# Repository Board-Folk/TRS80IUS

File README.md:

# TRS80IUS

A remake of the TRS-80 Model I 1700069G motherboard.

This reposistory contains the BOM, gerbers and Kicad files for a remake of the final 'G' version (as far as we know), of the TRS-80 Model I original American version motherboard and some related projects and files. This project spawned after publishing its sister project, a recreation of the [TEC, Japanese version which can be found here](https://github.com/Board-Folk/TRS80IJP).

This is intended as a replica, but additional headers have been provided for the common modification of the 8 bit character set - "BIT6" and "D6" - and "L8" for connection of a character ROM substitute like the Gendon3 module. If original operation with 7-bit characters is required, solder jumper UC should be connected. No additional factory bodge capacitors were added either, for example the ones for the horizontal and vertical sync stabalization. You'll still need to add those yourself.

## Version 1.1 Bill-of-Materials

All resistors 1/4W unless specified. Suggested substitutes might be wrong. Any feedback welcome.

|Qty|Reference(s)|Value|Type|Notes|
|:--:|:--:|:--:|:--:|:--:|
|1|C1|220uF 16V|Electrolytic Capacitor||
|6|C2, C4, C5, C10, C11, C57|10uF 16V|Electrolytic Capacitor||
|1|C6|100uF 16V|Electrolytic Capacitor||
|1|C8|2200uF 35V|Electrolytic Capacitor (Axial)||
|1|C9|10000uF 16V|Electrolytic Capacitor (Axial)||
|1|C42|22uF 16V|Electrolytic Capacitor||
|1|C26|0.047uF|Film Capacitor||
|1|C27|0.022uF|Film Capacitor||
|35|C16-C19, C22, C23, C28-C34, C35-C39, C40, C41, C44-C56, C58, C59|100nF|Ceramic Capacitor||
|4|C3, C7, C14, C15|10nF|Ceramic Capacitor||
|2|C12, C13|470pF|Ceramic Capacitor||
|1|C20|330pF|Ceramic Capacitor||
|1|C21|750pF|Ceramic Capacitor||
|2|C24, C25|220pF|Ceramic Capacitor||
|1|C43|47pF|Ceramic Capacitor||
|1|CR1|1N4735A|6.2V Zener Diode||
|1|CR2|1N4733A|5.1V Zener Diode||
|2|CR9, CR10|1N982|75V Zener Diode||
|5|CR3-CR7|1N4148|Small Signal Diode||
|1|CR8|S2V B20|Rectifier||
|1|Q1|MPS3904|Transistor TO-92||
|2|Q2, Q5|MPS3906|Transistor TO-92||
|1|Q3|TIP29A|Transistor TO-220||
|1|Q4|2N6594|Transistor TO-3|See Links|
|1|Q6|MJE34|Transistor TO-220|See Links|
|1|R18|5R6 3W|Resistor||
|1|R4|0R33 2W|Resistor||
|1|R1|68R 1/2W|Resistor||
|1|R19|220R 1/2W|Resistor||
|1|R2|2K7|Resistor||
|1|R3|750R|Resistor||
|2|R5, R10|1K|Potentiometer|Piher PT10LH01|
|4|R6, R7, R16, R53|1K2|Resistor||
|1|R8|100K|Resistor||
|3|R9, R11, R12|3K3|Resistor||
|1|R13|2K2|Resistor||
|1|R14|12K|Resistor||
|1|R15|1K5|Resistor||
|1|R17|2K|Resistor||
|2|R20, R21|100K|Potentiometer|Piher PT10LH01|
|1|R22|75R|Resistor||
|1|R23|120R|Resistor||
|1|R24|680K|Resistor||
|1|R25|1.8M|Resistor||
|2|R26, R42|1M|Resistor||
|2|R27, R64|330R|Resistor||
|1|R28|270R|Resistor||
|1|R29|1.8K|Resistor||
|1|R30|47R|Resistor||
|1|R31|10R|Resistor||
|5|R32, R43, R44, R47, R65|10K|Resistor||
|2|R33, R36|360K|Resistor||
|5|R34, R35, R38, R41, R45|470K|Resistor||
|1|R37|560K|Resistor||
|16|R39, R40, R48-R51, R57-R62, R66-R69|4K7|Resistor||
|2|R46, R52|910R|Resistor||
|2|R54, R55|7K5|Resistor||
|1|R56|220K|Resistor||
|1|R63|4.7K|Resistor||
|1|R167|100R|Resistor||
|1|Z40|Z80CPU|IC||
|1|Z29|MCM667X|IC|Character ROM|
|8|Z13-Z20|4116 RAM|IC||
|7|Z45-Z48, Z61-Z63|2102 RAM|IC|8 if modified for 8 bit characters|
|1|Z33|2364 ROM|IC||
|1|Z34|2332 ROM|IC||
|2|Z1, Z2|LM723|IC||
|1|Z41|75452|IC||
|1|Z4|LM3900N|IC||
|1|Z5|74C00|IC||
|2|Z6, Z57|74C04|IC||
|3|Z7, Z69, Z70|74LS74|IC||
|1|Z8|74LS153|IC||
|3|Z9, Z42, Z52|74LS04|IC||
|2|Z10, Z11|74LS166|IC||
|4|Z12, Z32, Z50, Z65|74LS93|IC||
|1|Z21|74LS156|IC||
|11|Z22, Z38, Z39, Z44, Z55, Z60, Z67, Z68, Z72, Z75, Z76|74LS367|IC||
|4|Z23, Z25, Z36, Z73|74LS32|IC||
|2|Z24, Z53|74LS132|IC||
|1|Z26|74LS20|IC||
|2|Z27, Z59|74LS175|IC||
|1|Z28|74LS174|IC||
|2|Z30, Z37|74LS02|IC||
|6|Z31, Z35, Z43, Z49, Z51, Z64|74LS157|IC||
|1|Z54|74LS30|IC||
|2|Z56, Z58|74LS92|IC||
|1|Z66|74LS11|IC||
|1|Z74|74LS00|IC||
|1|Y1|10.6445MHz HC-49 Crystal|Crystal Oscillator|See Links|
|2|Z3, Z71|DIP16 Switch or Jumper Block|Switch||
|1|S1|Power Switch|Switch|Information to follow|
|1|S2|Reset Switch|Switch|Information to follow|
|3|J1,J2,J3|DIN5 180-degree Socket|Socket||
|1|K1|5V Reed Relay|Relay|Sensata-Cynergy3 S2-05P|

## Links

  [10.6445Mhz HC49U Quartz Crystal (UK)](https://www.mutant-caterpillar.co.uk/shop/product_info.php?products_id=5174)<br>
  [MJ15016 Transistor (Q4 Substitute) (UK)](https://www.cricklewoodelectronics.com/MJ15016.html)<br>
  [MJE15031 Transistor (Q6 Substitute) (UK)](https://www.cricklewoodelectronics.com/MJE15031.html)

## Credits

PCB Layout by Rob Taylor @peepouk. Schematics recreated by Ian Cudlip @grandoldian.

## Thanks

  * Chrissy @chris_jh and the rest of the Board Folk Team.
  * Adrian Black and friends for their test ROM which has been invaluable during testing. [TRS-80 Diagnostic ROM](https://github.com/misterblack1/trs80-diagnosticrom).

## Legal

As the product of this project is a replica of a proprietary product, the the author makes no claim of copyright to the schematics nor PCB layouts and releases these into the public domain, solely for the purposes of study and historical preservation.

You are free to produce PCBs based on this project's designs at your own risk and without limitation, for your own use or for sale and/or repair at a reasonable price. Attribution is appreciated. The authors are not obliged to provide support of any kind. 

Under no circumstances will the authors be held responsible or liable in any way for losses, damages or costs resulting from the use of the information and/or resources of this project. 

The resources are provided "as-is" without warranty of any kind, either expressed or implied, including, but not limited to, the implied warranties of merchantability and fitness for a particular purpose.

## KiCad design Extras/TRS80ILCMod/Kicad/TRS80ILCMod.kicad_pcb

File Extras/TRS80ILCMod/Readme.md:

# TRS80ILCMod Lower Case (8-bit) Adapter Board

This avoids the need to piggy back two 2102 video RAM chips, allowing for their installation side by side over a single socket with connections to the board on 'bit6' and 'd6', found as headers on our replica board. Could be used on an original board if you locate the right pins.

Just needs 2 of 8 pin round pin headers, two DIP16 sockets (unless you're feeling brave), a 5mm decoupling capacitor e.g. 100nF and two wire connections to bit6 (pin 1) and d6 (pin 2).

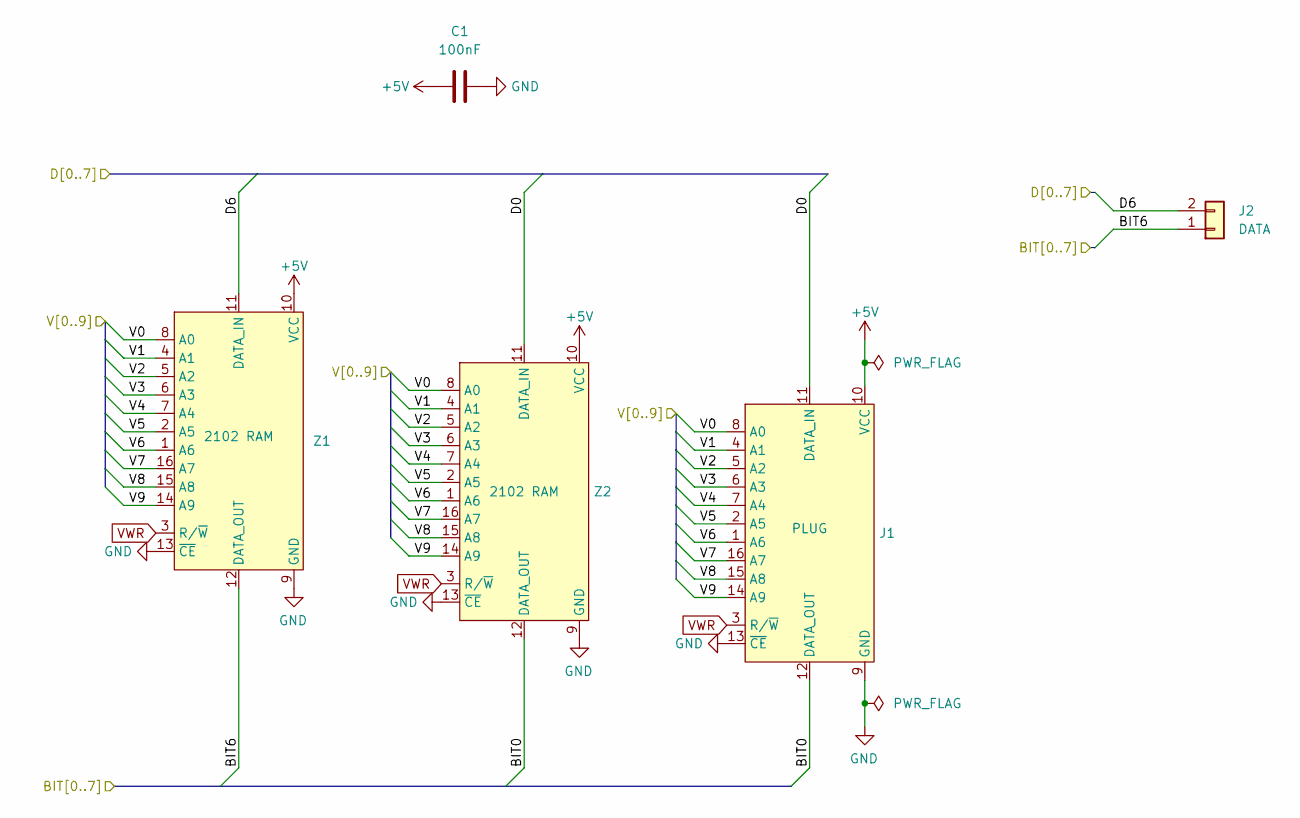
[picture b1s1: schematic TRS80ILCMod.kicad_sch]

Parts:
C1: 100nF; Ceramic Disc 6.35mm
J1: PLUG; VRAMPLUG
J2: DATA; PinHeader_1x02_P2.54mm_Vertical
Z1, Z2: 2102 RAM; DIP-16_W7.62mm

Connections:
+5V: C1.1, J1.10 (VCC), Z1.10 (VCC), Z2.10 (VCC)
/BIT0: J1.12 (DATA_OUT), Z2.12 (DATA_OUT)
/BIT6: J2.1, Z1.12 (DATA_OUT)
/D0: J1.11 (DATA_IN), Z2.11 (DATA_IN)
/D6: J2.2, Z1.11 (DATA_IN)
/V0: J1.8 (A0), Z1.8 (A0), Z2.8 (A0)
/V1: J1.4 (A1), Z1.4 (A1), Z2.4 (A1)
/V2: J1.5 (A2), Z1.5 (A2), Z2.5 (A2)
/V3: J1.6 (A3), Z1.6 (A3), Z2.6 (A3)
/V4: J1.7 (A4), Z1.7 (A4), Z2.7 (A4)
/V5: J1.2 (A5), Z1.2 (A5), Z2.2 (A5)
/V6: J1.1 (A6), Z1.1 (A6), Z2.1 (A6)
/V7: J1.16 (A7), Z1.16 (A7), Z2.16 (A7)
/V8: J1.15 (A8), Z1.15 (A8), Z2.15 (A8)
/V9: J1.14 (A9), Z1.14 (A9), Z2.14 (A9)
GND: C1.2, J1.9 (GND), J1.13 (~CE), Z1.9 (GND), Z1.13 (~CE), Z2.9 (GND), Z2.13 (~CE)
VWR: J1.3 (R/~W), Z1.3 (R/~W), Z2.3 (R/~W)

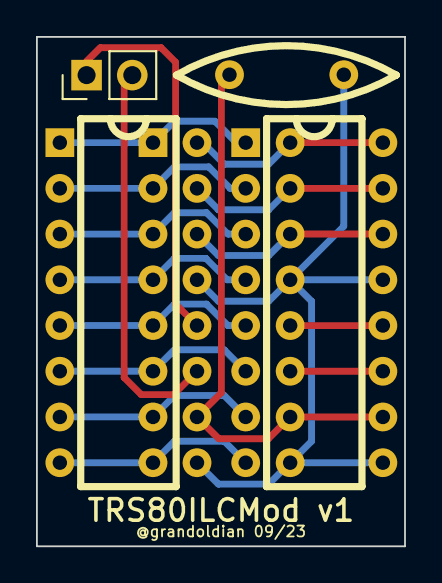
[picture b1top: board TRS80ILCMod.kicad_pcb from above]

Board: 2 copper layers, 20.5 x 28.3 mm, 5 parts (0 on the bottom side), 17 nets.

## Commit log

2023-12-29 Kicad and Readme Update
2023-12-29 LCMod
2023-12-29 Readme update
